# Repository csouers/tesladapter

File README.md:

# tesladapter
Adapt tesla bosch radar to honda bosch (or others)

To use tesla radar with honda bosch cars. Breakout available for testing/debug or adapting to other cars.

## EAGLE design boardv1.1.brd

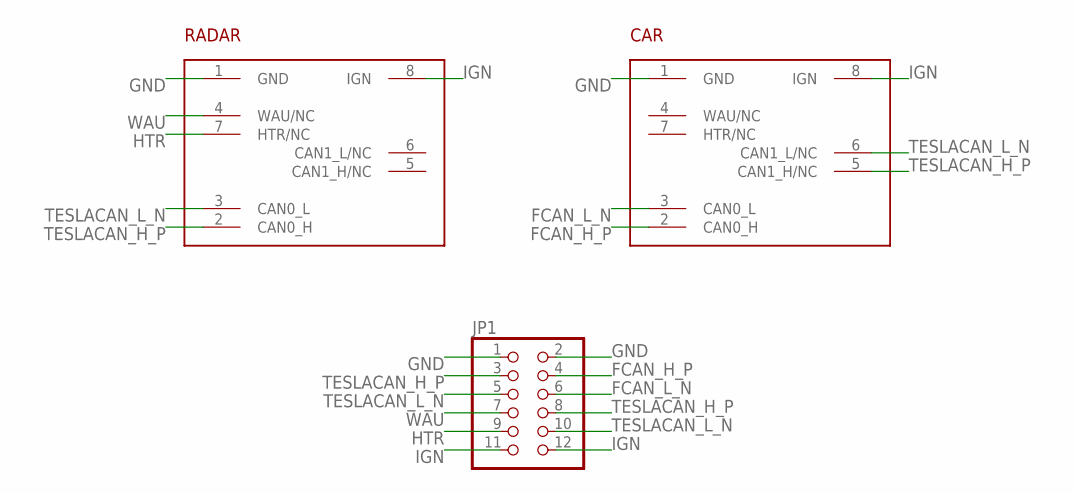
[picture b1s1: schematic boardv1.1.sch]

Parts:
CAR: TE_AMP_1-967658-1
JP1: PINHD-2X6/90; 2X06/90
RADAR: TE_AMP_1-1534229-1TESLARADAR; TE_AMP_1-1534229-1

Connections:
FCAN_H_P: CAR.2 (CAN0_H), JP1.4
FCAN_L_N: CAR.3 (CAN0_L), JP1.6
GND: CAR.1 (GND), JP1.1, JP1.2, RADAR.1 (GND)
HTR: JP1.9, RADAR.7 (HTR/NC)
IGN: CAR.8 (IGN), JP1.11, JP1.12, RADAR.8 (IGN)
TESLACAN_H_P: CAR.5 (CAN1_H/NC), JP1.3, JP1.8, RADAR.2 (CAN0_H)
TESLACAN_L_N: CAR.6 (CAN1_L/NC), JP1.5, JP1.10, RADAR.3 (CAN0_L)
WAU: JP1.7, RADAR.4 (WAU/NC)

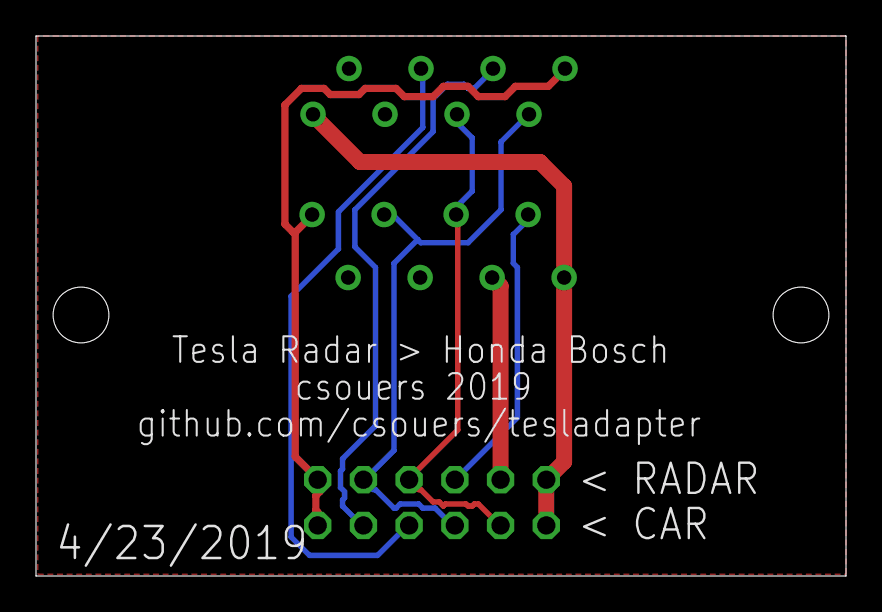
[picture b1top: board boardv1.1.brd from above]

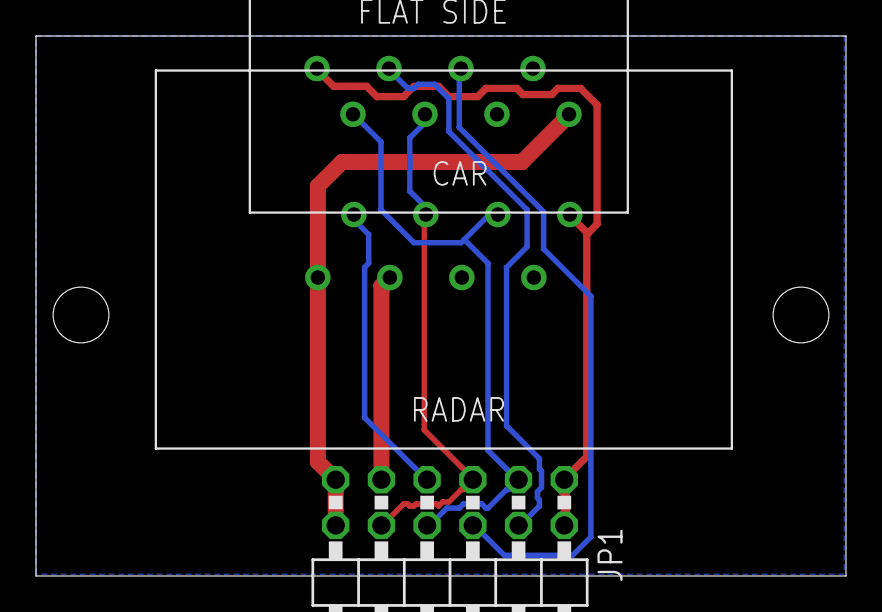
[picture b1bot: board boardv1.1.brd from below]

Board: 2 copper layers, 45.0 x 30.0 mm, 3 parts (3 on the bottom side), 8 nets.

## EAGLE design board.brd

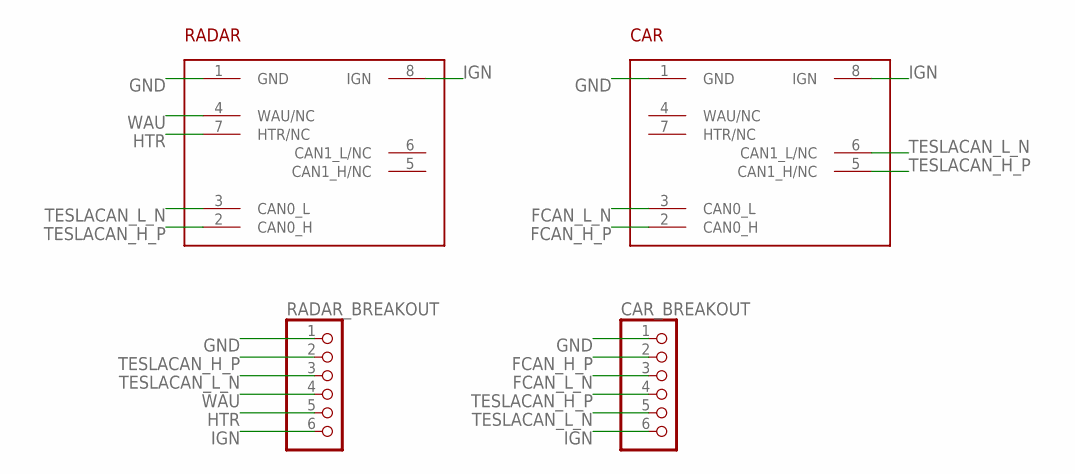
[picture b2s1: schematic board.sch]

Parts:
CAR: TE_AMP_1-967658-1
CAR_BREAKOUT: PINHD-1X6; 1X06
RADAR: TE_AMP_1-1534229-1TESLARADAR; TE_AMP_1-1534229-1
RADAR_BREAKOUT: PINHD-1X6; 1X06

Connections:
FCAN_H_P: CAR.2 (CAN0_H), CAR_BREAKOUT.2
FCAN_L_N: CAR.3 (CAN0_L), CAR_BREAKOUT.3
GND: CAR.1 (GND), CAR_BREAKOUT.1, RADAR.1 (GND), RADAR_BREAKOUT.1
HTR: RADAR.7 (HTR/NC), RADAR_BREAKOUT.5
IGN: CAR.8 (IGN), CAR_BREAKOUT.6, RADAR.8 (IGN), RADAR_BREAKOUT.6
TESLACAN_H_P: CAR.5 (CAN1_H/NC), CAR_BREAKOUT.4, RADAR.2 (CAN0_H), RADAR_BREAKOUT.2
TESLACAN_L_N: CAR.6 (CAN1_L/NC), CAR_BREAKOUT.5, RADAR.3 (CAN0_L), RADAR_BREAKOUT.3
WAU: RADAR.4 (WAU/NC), RADAR_BREAKOUT.4

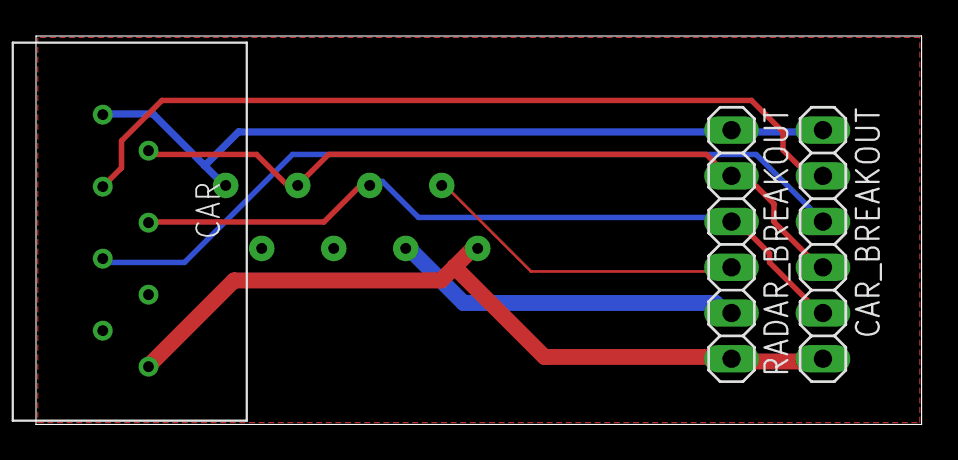
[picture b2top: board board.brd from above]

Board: 2 copper layers, 49.2 x 21.6 mm, 4 parts (1 on the bottom side), 8 nets.

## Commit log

2019-04-16 board
2019-04-18 v0.2
2019-05-03 i had this one made. should work.
    Use the 1.1 files. The old stuff is old and probably wont work and whatnot
